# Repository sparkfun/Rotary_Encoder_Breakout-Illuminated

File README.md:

SparkFun Rotary Encoder Breakout - Illuminated (RG/RGB)
=======================================================

[*SparkFun Rotary Encoder Breakout - Illuminated (RG/RGB) (BOB-11722)*](https://www.sparkfun.com/products/11722)

This is a clever little breakout board for both the RGB and R/G illuminated rotary encoders. 
On one side, it breaks out all of the RGB pins to standard, breadboard friendly, 0.1" headers. 
Turn it over and it has a footprint for the R/G version! 

Repository Contents
-------------------
* **/Firmware** - Example for the RGB and RG Rotary Encoders
* **/Hardware** - Eagle design files (.brd, .sch)
* **/Libraries** - Archived library of the PinChangeInt used for the example code

Documentation
--------------
* **[Installing an Arduino Library Guide](https://learn.sparkfun.com/tutorials/installing-an-arduino-library/all#manually-installing-a-library---windows)** - Basic information on how to install an Arduino library. You will need to manually install the PinChangeInt Arduino library.
* **[SparkFun Fritzing repo](https://github.com/sparkfun/Fritzing_Parts)** - Fritzing diagrams for SparkFun products.
* **[SparkFun 3D Model repo](https://github.com/sparkfun/3D_Models)** - 3D models of SparkFun products. 

Product Versions
----------------

Compatible with the following rotary encoders: 

* [COM-15141](https://www.sparkfun.com/products/15141) - RGB rotary encoder - illuminated; buttons and LEDs are common cathode
* [COM-15140](https://www.sparkfun.com/products/15140) - RG rotary encoder - illuminated, buttons and LEDs are common anode
* _[COM-10982 (retired)](https://www.sparkfun.com/products/10982) - RGB rotary encoder - illuminated; buttons and LEDs are common cathode_
* _[COM-10596 (retired)](https://www.sparkfun.com/products/10596) - RG rotary encoder - illuminated, buttons and LEDs are common anode_

License Information
-------------------
This product is _**open source**_! 

The **hardware** is released under [Creative Commons ShareAlike 4.0 International](https://creativecommons.org/licenses/by-sa/4.0/).

Please use, reuse, and modify these files as you see fit. Please maintain attribution to SparkFun Electronics and release anything derivative under the same license.

Distributed as-is; no warranty is given.

- Your friends at SparkFun.

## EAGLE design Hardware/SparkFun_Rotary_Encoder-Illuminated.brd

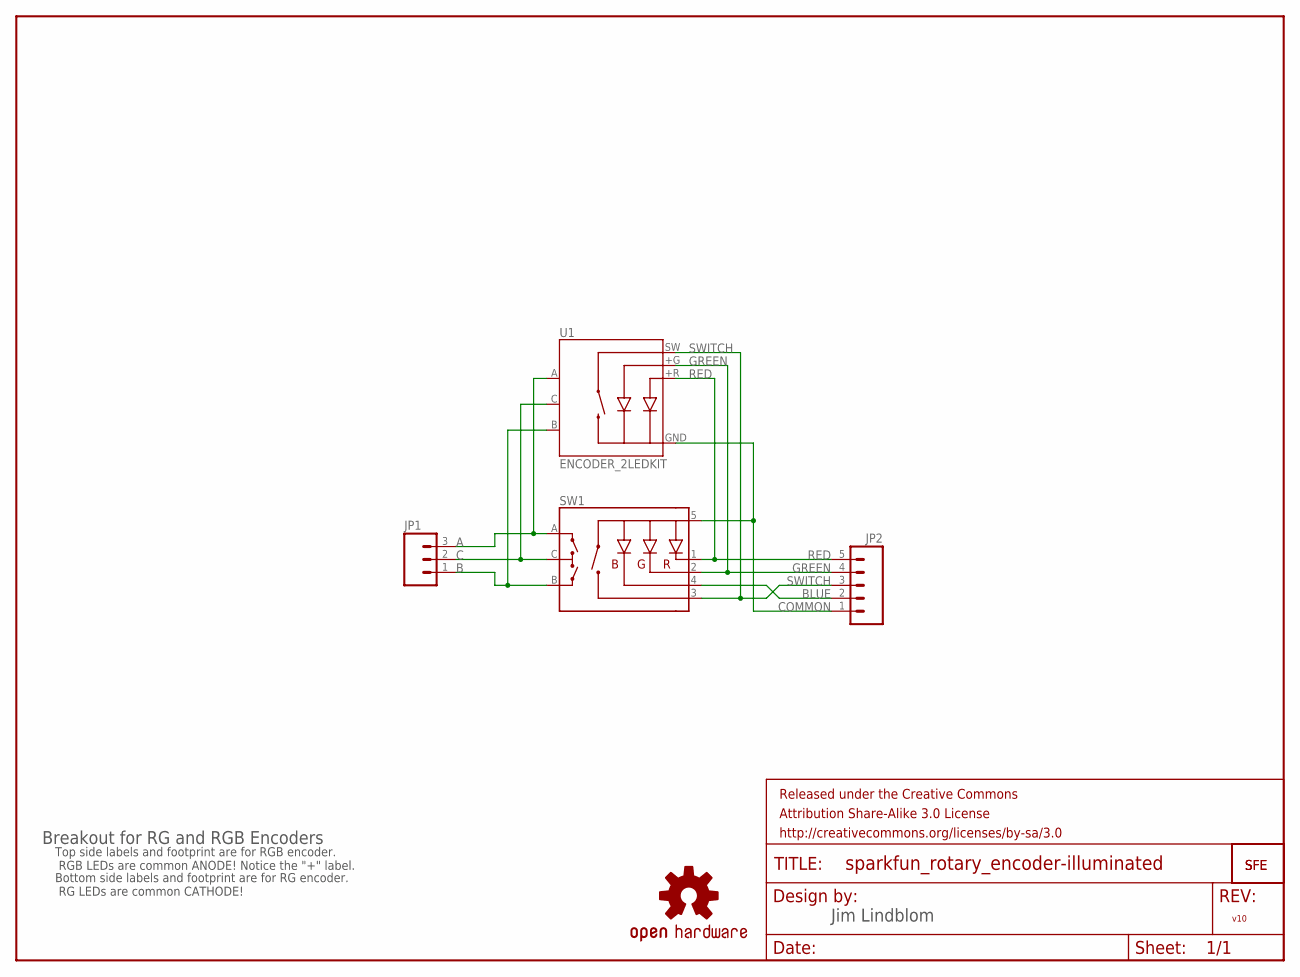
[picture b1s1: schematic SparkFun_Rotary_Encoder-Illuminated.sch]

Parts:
FRAME1: FRAME-LETTER; CREATIVE_COMMONS
JP1: M03PTH; 1X03
JP2: M05PTH; 1X05
JP3, JP4: LOGO-SFESK; SFE-LOGO-FLAME
SW1: ENCODER_RGB_CAKIT; ENCODER_LED_3_KIT
U1: ENCODER_2LEDKIT; ENCODER_LED_2_KIT
U$2: OSHW-LOGOS; OSHW-LOGO-S

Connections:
A: JP1.3, SW1.A, U1.A
B: JP1.1, SW1.B, U1.B
BLUE: JP2.2, SW1.4 (-B)
C: JP1.2, SW1.C, U1.C
COMMON: JP2.1, SW1.5 (+), U1.GND (-)
GREEN: JP2.4, SW1.2 (-G), U1.+G
RED: JP2.5, SW1.1 (-R), U1.+R
SWITCH: JP2.3, SW1.3 (SW), U1.SW

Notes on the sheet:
Jim Lindblom
Breakout for RG and RGB Encoders
Top side labels and footprint are for RGB encoder. RGB LEDs are common ANODE! Notice the "+" label.
Bottom side labels and footprint are for RG encoder. RG LEDs are common CATHODE!
v10

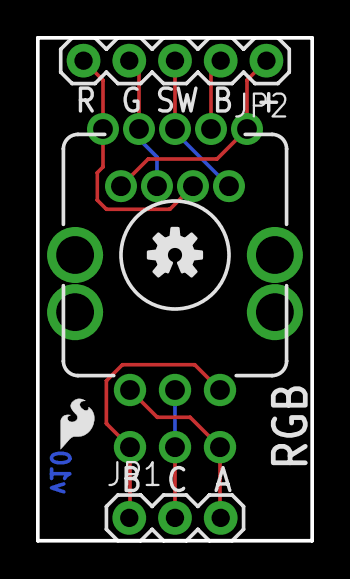
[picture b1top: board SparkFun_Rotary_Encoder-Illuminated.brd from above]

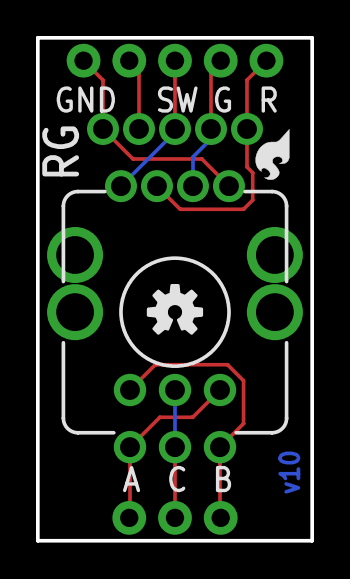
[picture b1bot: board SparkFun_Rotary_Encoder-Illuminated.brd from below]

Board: 2 copper layers, 15.2 x 27.9 mm, 9 parts (3 on the bottom side), 8 nets.

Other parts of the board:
U$1: OSHW-LOGOS; OSHW-LOGO-S

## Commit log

2015-05-04 Adding README info, updating product files
2015-05-04 Fixing picture URL in README
2018-12-20 Example Code for RGB Rotary Encoder
    Add example code for the RGB Rotary Encoder
    Add library used with example code.
2018-12-20 Turn LED to White on Start
2019-01-04 Create RG_Rotary_Encoder_Demo.ino
    Logic is reversed in this version of code since the RG Rotary Switch is a common anode instead of common cathode. Blue is commented out since it is not being used. The switch will be using a pullUP r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
2019-01-04 Moving RG Rotary Encoder Demo into Firmware Folder
2019-01-04 Update File Names And Notes
2021-04-30 Use EnableInterrupt lib, INPUT_PULLUP, and other little fixes
    This only changes RG_Rotary_Encoder but most changes
    probably should apply to RGB_Rotary_Encoder as well but
    I don't have one to test.
    - Sets input pins to INPUT_PULLUP
    - Replaces usage of PinChangeInt lib in favor of EnableInterrupt
    - Uses faster serial speed

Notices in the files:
parts and their libraries:
SparkFun-Electromechanical: Licensing: CC v3.0 Share-Alike You are welcome to use this library for commercial purposes.
SparkFun-Aesthetics: Released under the Creative Commons Attribution Share-Alike 3.0 License
SparkFun-Aesthetics: http://creativecommons.org/licenses/by-sa/3.0
